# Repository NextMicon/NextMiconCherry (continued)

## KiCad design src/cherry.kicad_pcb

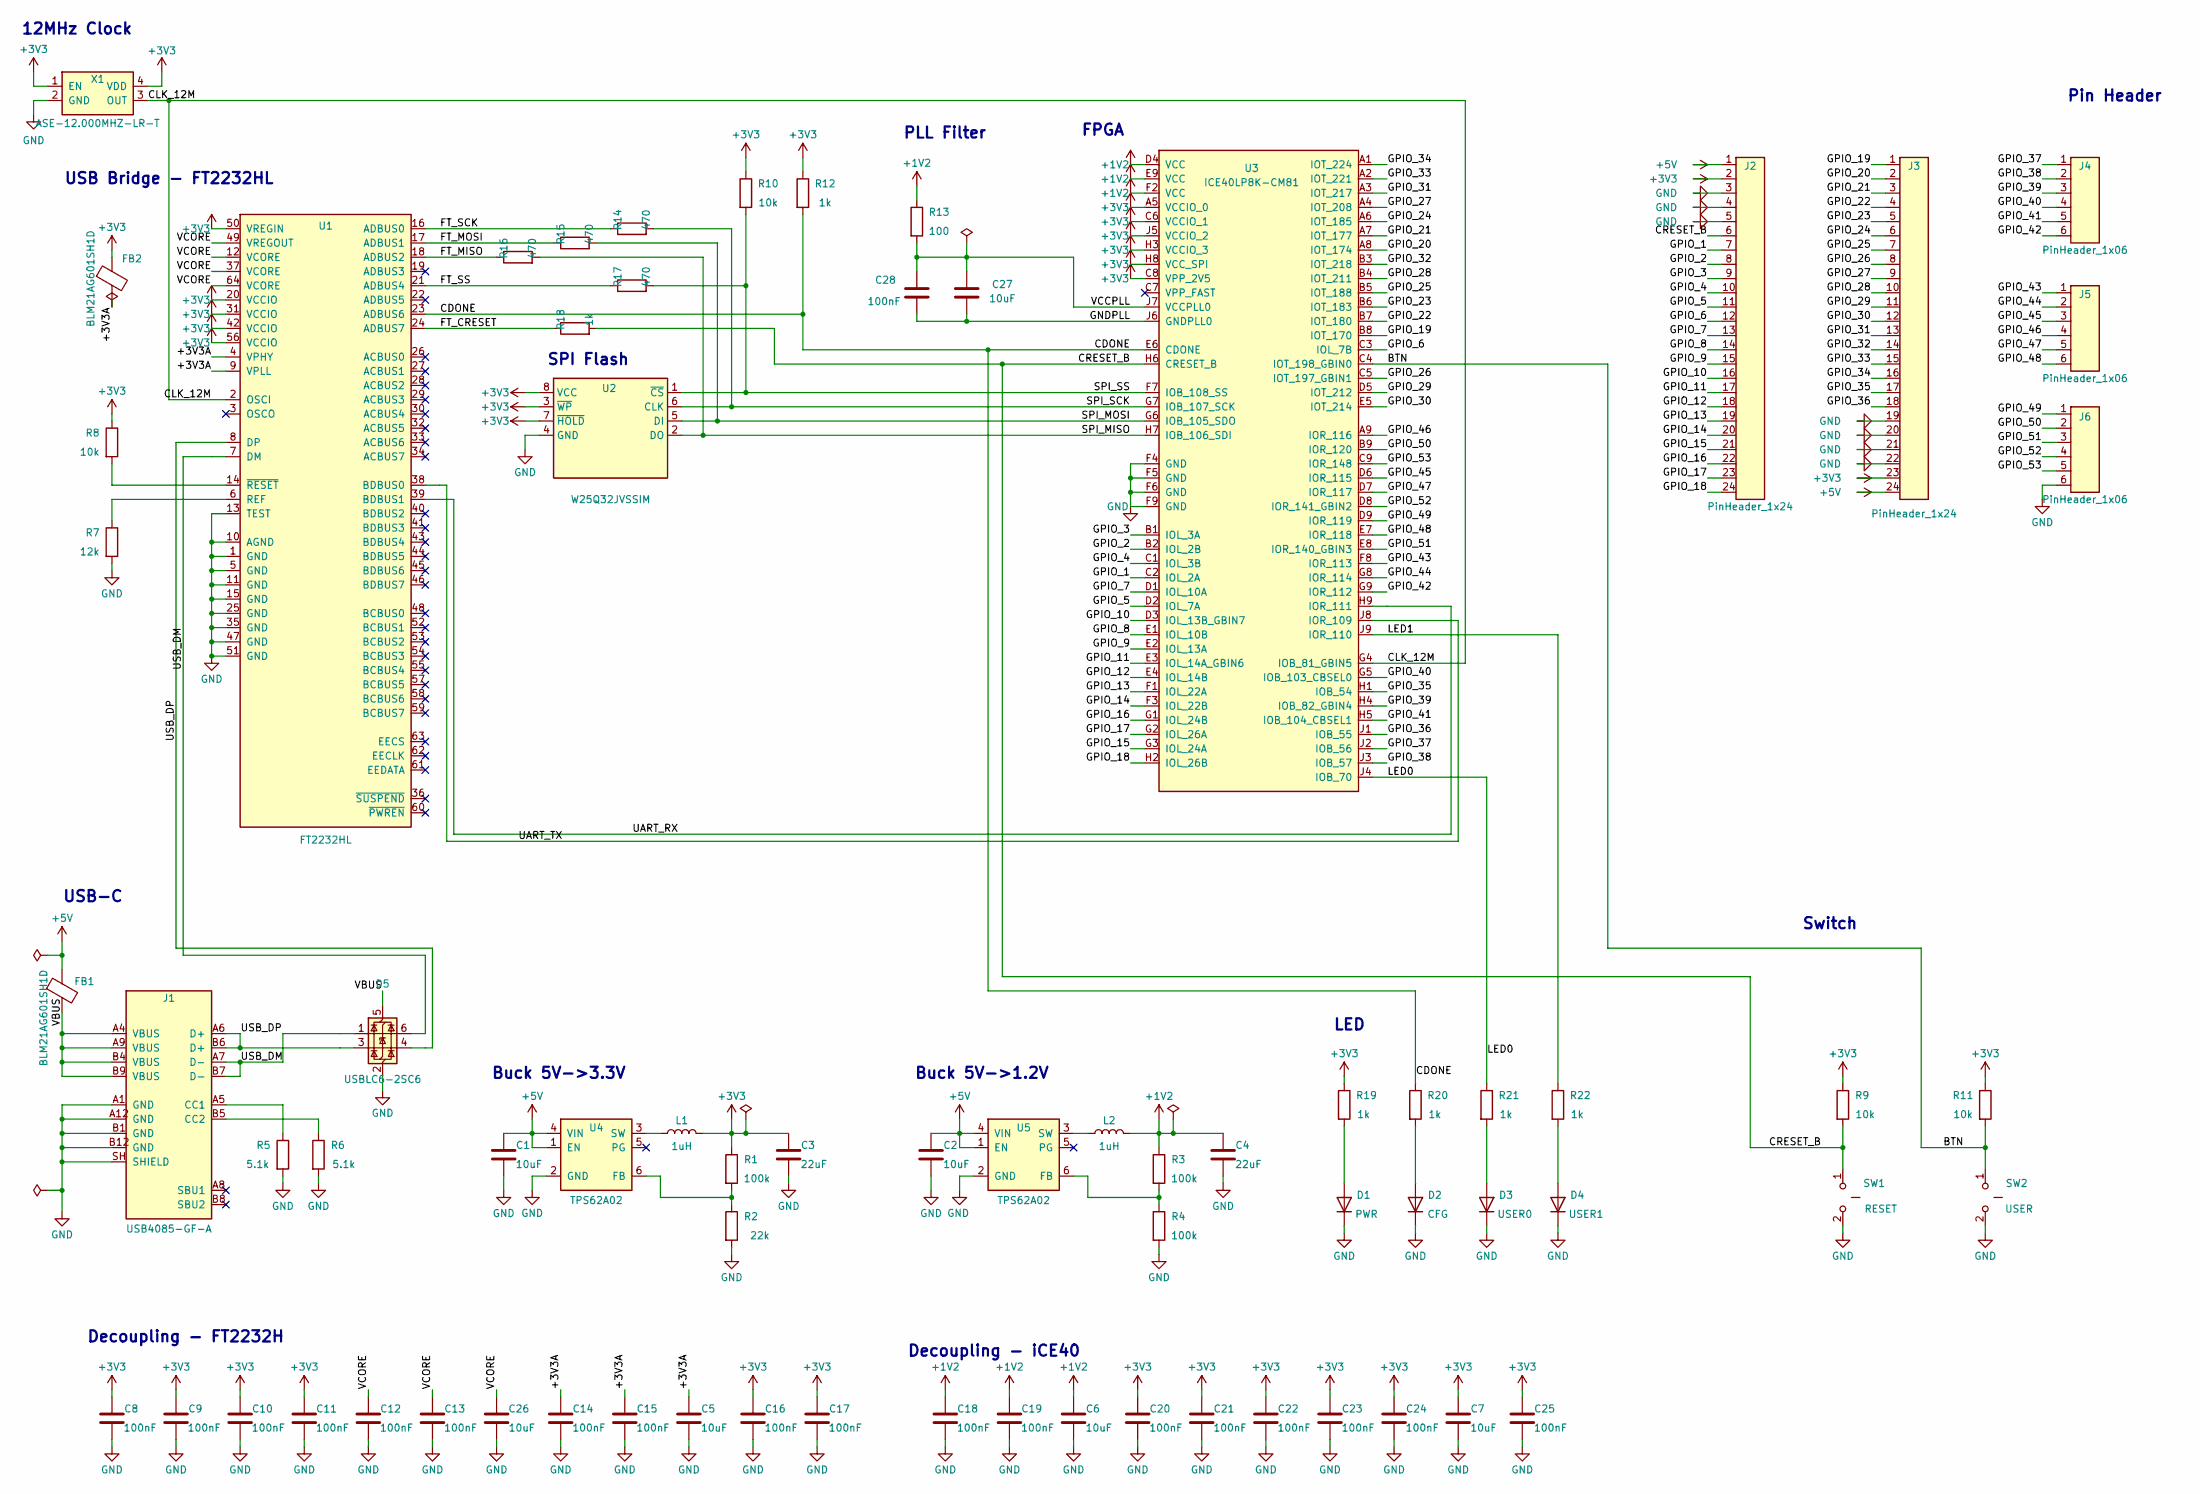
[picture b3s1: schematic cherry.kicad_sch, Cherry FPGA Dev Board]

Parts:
C1, C2, C5, C6, C7, C26, C27: 10uF; C_0805_2012Metric
C3, C4: 22uF; C_0805_2012Metric
C8, C9, C10, C11, C12, C13, C14, C15, C16, C17, C18, C19, C20, C21, C22, C23, C24, C25, C28: 100nF; C_0402_1005Metric
D1: PWR; LED_0603_1608Metric
D2: CFG; LED_0603_1608Metric
D3: USER0; LED_0603_1608Metric
D4: USER1; LED_0603_1608Metric
D5: USBLC6-2SC6; SOT-23-6
FB1, FB2: BLM21AG601SH1D; L_0805_2012Metric
J1: USB4085-GF-A; USB_C_Receptacle_GCT_USB4085
J2, J3: PinHeader_1x24; PinHeader_1x24_P2.54mm
J4, J5, J6: PinHeader_1x06; PinHeader_1x06_P2.54mm
L1, L2: 1uH; L_0805_2012Metric
R1, R3, R4: 100k; R_0402_1005Metric
R2: 22k; R_0402_1005Metric
R5, R6: 5.1k; R_0402_1005Metric
R7: 12k; R_0402_1005Metric
R8, R9, R10, R11: 10k; R_0402_1005Metric
R12, R18, R19, R20, R21, R22: 1k; R_0402_1005Metric
R13: 100; R_0402_1005Metric
R14, R15, R16, R17: 470; R_0402_1005Metric
SW1: RESET; SW_Push_1P1T_NO_CK_KMR2
SW2: USER; SW_Push_1P1T_NO_CK_KMR2
U1: FT2232HL; LQFP-64_10x10mm_P0.5mm
U2: W25Q32JVSSIM; SOIC-8_5.3x5.3mm_P1.27mm
U3: ICE40LP8K-CM81; BGA-81_9x9_8.0x8.0mm_P0.8mm
U4, U5: TPS62A02; SOT-23-6
X1: ASE-12.000MHZ-LR-T; Oscillator_SMD_Abracon_ASE-4Pin_3.2x2.5mm

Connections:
+1V2: C4.1, C6.1, C18.1, C19.1, L2.2, R3.1, R13.1, U3.D4 (VCC), U3.E9 (VCC), U3.F2 (VCC)
+3V3: C3.1, C7.1, C8.1, C9.1, C10.1, C11.1, C16.1, C17.1, C20.1, C21.1, C22.1, C23.1, C24.1, C25.1, FB2.1, J2.2, J3.23, L1.2, R1.1, R8.1, R9.1, R10.1, R11.1, R12.1, R19.1, U1.20 (VCCIO), U1.31 (VCCIO), U1.42 (VCCIO), U1.50 (VREGIN), U1.56 (VCCIO), U2.3 (~WP), U2.7 (~HOLD), U2.8 (VCC), U3.A5 (VCCIO_0), U3.C6 (VCCIO_1), U3.C8 (VPP_2V5), U3.H3 (VCCIO_3), U3.H8 (VCC_SPI), U3.J5 (VCCIO_2), X1.1 (EN), X1.4 (VDD)
+5V: C1.1, C2.1, FB1.1, J2.1, J3.24, U4.1 (EN), U4.4 (VIN), U5.1 (EN), U5.4 (VIN)
/+3V3A: C5.1, C14.1, C15.1, FB2.2, U1.4 (VPHY), U1.9 (VPLL)
/BTN: R11.2, SW2.1, U3.C4 (IOT_198_GBIN0)
/CDONE: R12.2, R20.1, U1.23 (ADBUS6), U3.E6 (CDONE)
/CLK_12M: U1.2 (OSCI), U3.G4 (IOB_81_GBIN5), X1.3 (OUT)
/CRESET_B: J2.6, R9.2, R18.2, SW1.1, U3.H6 (CRESET_B)
/FT_CRESET: R18.1, U1.24 (ADBUS7)
/FT_MISO: R16.1, U1.18 (ADBUS2)
/FT_MOSI: R15.1, U1.17 (ADBUS1)
/FT_SCK: R14.1, U1.16 (ADBUS0)
/FT_SS: R17.1, U1.21 (ADBUS4)
/GNDPLL: C27.2, C28.2, U3.J6 (GNDPLL0)
/GPIO_1: J2.7, U3.C2 (IOL_2A)
/GPIO_2: J2.8, U3.B2 (IOL_2B)
/GPIO_3: J2.9, U3.B1 (IOL_3A)
/GPIO_4: J2.10, U3.C1 (IOL_3B)
/GPIO_5: J2.11, U3.D2 (IOL_7A)
/GPIO_6: J2.12, U3.C3 (IOL_7B)
/GPIO_7: J2.13, U3.D1 (IOL_10A)
/GPIO_8: J2.14, U3.E1 (IOL_10B)
/GPIO_9: J2.15, U3.E2 (IOL_13A)
/GPIO_10: J2.16, U3.D3 (IOL_13B_GBIN7)
/GPIO_11: J2.17, U3.E3 (IOL_14A_GBIN6)
/GPIO_12: J2.18, U3.E4 (IOL_14B)
/GPIO_13: J2.19, U3.F1 (IOL_22A)
/GPIO_14: J2.20, U3.F3 (IOL_22B)
/GPIO_15: J2.21, U3.G3 (IOL_24A)
/GPIO_16: J2.22, U3.G1 (IOL_24B)
/GPIO_17: J2.23, U3.G2 (IOL_26A)
/GPIO_18: J2.24, U3.H2 (IOL_26B)
/GPIO_19: J3.1, U3.B8 (IOT_170)
/GPIO_20: J3.2, U3.A8 (IOT_174)
/GPIO_21: J3.3, U3.A7 (IOT_177)
/GPIO_22: J3.4, U3.B7 (IOT_180)
/GPIO_23: J3.5, U3.B6 (IOT_183)
/GPIO_24: J3.6, U3.A6 (IOT_185)
/GPIO_25: J3.7, U3.B5 (IOT_188)
/GPIO_26: J3.8, U3.C5 (IOT_197_GBIN1)
/GPIO_27: J3.9, U3.A4 (IOT_208)
/GPIO_28: J3.10, U3.B4 (IOT_211)
/GPIO_29: J3.11, U3.D5 (IOT_212)
/GPIO_30: J3.12, U3.E5 (IOT_214)
/GPIO_31: J3.13, U3.A3 (IOT_217)
/GPIO_32: J3.14, U3.B3 (IOT_218)
/GPIO_33: J3.15, U3.A2 (IOT_221)
/GPIO_34: J3.16, U3.A1 (IOT_224)
/GPIO_35: J3.17, U3.H1 (IOB_54)
/GPIO_36: J3.18, U3.J1 (IOB_55)
/GPIO_37: J4.1, U3.J2 (IOB_56)
/GPIO_38: J4.2, U3.J3 (IOB_57)
/GPIO_39: J4.3, U3.H4 (IOB_82_GBIN4)
/GPIO_40: J4.4, U3.G5 (IOB_103_CBSEL0)
/GPIO_41: J4.5, U3.H5 (IOB_104_CBSEL1)
/GPIO_42: J4.6, U3.G9 (IOR_112)
/GPIO_43: J5.1, U3.F8 (IOR_113)
/GPIO_44: J5.2, U3.G8 (IOR_114)
/GPIO_45: J5.3, U3.D6 (IOR_115)
/GPIO_46: J5.4, U3.A9 (IOR_116)
/GPIO_47: J5.5, U3.D7 (IOR_117)
/GPIO_48: J5.6, U3.E7 (IOR_118)
/GPIO_49: J6.1, U3.D9 (IOR_119)
/GPIO_50: J6.2, U3.B9 (IOR_120)
/GPIO_51: J6.3, U3.E8 (IOR_140_GBIN3)
/GPIO_52: J6.4, U3.D8 (IOR_141_GBIN2)
/GPIO_53: J6.5, U3.C9 (IOR_148)
/LED0: R21.1, U3.J4 (IOB_70)
/LED1: R22.1, U3.J9 (IOR_110)
/SPI_MISO: R16.2, U2.2 (DO), U3.H7 (IOB_106_SDI)
/SPI_MOSI: R15.2, U2.5 (DI), U3.G6 (IOB_105_SDO)
/SPI_SCK: R14.2, U2.6 (CLK), U3.G7 (IOB_107_SCK)
/SPI_SS: R10.2, R17.2, U2.1 (~CS), U3.F7 (IOB_108_SS)
/UART_RX: U1.39 (BDBUS1), U3.H9 (IOR_111)
/UART_TX: U1.38 (BDBUS0), U3.J8 (IOR_109)
/USB_DM: D5.1 (I/O1), D5.6 (I/O1), J1.A7 (D-), J1.B7 (D-), U1.7 (DM)
/USB_DP: D5.3 (I/O2), D5.4 (I/O2), J1.A6 (D+), J1.B6 (D+), U1.8 (DP)
/VBUS: D5.5 (VBUS), FB1.2, J1.A4 (VBUS), J1.A9 (VBUS), J1.B4 (VBUS), J1.B9 (VBUS)
/VCCPLL: C27.1, C28.1, R13.2, U3.J7 (VCCPLL0)
/VCORE: C12.1, C13.1, C26.1, U1.12 (VCORE), U1.37 (VCORE), U1.49 (VREGOUT), U1.64 (VCORE)
GND: C1.2, C2.2, C3.2, C4.2, C5.2, C6.2, C7.2, C8.2, C9.2, C10.2, C11.2, C12.2, C13.2, C14.2, C15.2, C16.2, C17.2, C18.2, C19.2, C20.2, C21.2, C22.2, C23.2, C24.2, C25.2, C26.2, D1.1 (K), D2.1 (K), D3.1 (K), D4.1 (K), D5.2 (GND), J1.A1 (GND), J1.A12 (GND), J1.B1 (GND), J1.B12 (GND), J1.SH (SHIELD), J2.3, J2.4, J2.5, J3.19, J3.20, J3.21, J3.22, J6.6, R2.2, R4.2, R5.2, R6.2, R7.2, SW1.2, SW2.2, U1.1 (GND), U1.5 (GND), U1.10 (AGND), U1.11 (GND), U1.13 (TEST), U1.15 (GND), U1.25 (GND), U1.35 (GND), U1.47 (GND), U1.51 (GND), U2.4 (GND), U3.F4 (GND), U3.F5 (GND), U3.F6 (GND), U3.F9 (GND), U4.2 (GND), U5.2 (GND), X1.2 (GND)
unnamed: D1.2 (A), R19.2
unnamed: D2.2 (A), R20.2
unnamed: D3.2 (A), R21.2
unnamed: D4.2 (A), R22.2
unnamed: J1.A5 (CC1), R5.1
unnamed: J1.B5 (CC2), R6.1
unnamed: R7.1, U1.6 (REF)
unnamed: R8.2, U1.14 (~RESET)
unnamed: R1.2, R2.1, U4.6 (FB)
unnamed: L1.1, U4.3 (SW)
unnamed: R3.2, R4.1, U5.6 (FB)
unnamed: L2.1, U5.3 (SW)

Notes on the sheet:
Switch
Buck 5V->3.3V
Decoupling - FT2232H
Pin Header
USB Bridge - FT2232HL
Buck 5V->1.2V
FPGA
PLL Filter
LED
USB-C
12MHz Clock
SPI Flash
Decoupling - iCE40

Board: 4 copper layers, 73 parts (5 on the bottom side), 93 nets, no tracks yet.

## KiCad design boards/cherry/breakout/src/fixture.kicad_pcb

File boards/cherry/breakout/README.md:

# Cherry Pmod breakout board

Cherryのピンヘッダ(J2/J3/J4)を上から**ピンソケット(S2/S3/S4)に挿し込み**、全64本のGPIOを8ポートのPmod(2×6、12ピン)として引き出すブレークアウト基板です。工場テスト(factory-test.sh)と、Pmodモジュールを挿しての動作確認の両方に使えます。

## ポート構成

| ポート | GPIO | 位置 |
| ------ | ---------- | -------- |
| PMOD1  | GPIO_1-8   | 下辺 左 |
| PMOD2  | GPIO_9-16  | 下辺 中左 |
| PMOD3  | GPIO_17-24 | 下辺 中右 |
| PMOD4  | GPIO_25-32 | 下辺 右 |
| PMOD5  | GPIO_33-40 | 上辺 右 |
| PMOD6  | GPIO_41-48 | 上辺 中右 |
| PMOD7  | GPIO_49-56 | 上辺 中左 |
| PMOD8  | GPIO_57-64 | 上辺 左 |

Cherry側のGPIOはブロック対配置(D0-D3が内側列、D4-D7がその対向の外側列)なので、各Pmodポートは Cherry の1つの2×4ブロックにそのまま対応します。各ポートのピン配置はPmod標準どおり: 1-4 = D0-D3、5 = GND、6 = 3V3、7-10 = D4-D7、11 = GND、12 = 3V3。D0が各ブロックの最小GPIO番号です(例: PMOD5のD0 = GPIO_33)。Pmodソケットは2×6のライトアングル・メスを基板端向きに実装します(実装前にピン1の向きをシルクの角パッドで確認してください)。

- S2/S3: 2×24ピンソケット。Cherry J2/J3が挿さります(ソケットのピン番号 = Cherryのパッド番号)。
- S4: 1×6ピンソケット。Cherry J4が挿さります。
- J5: Cherry J4のSPI/CRESET/GNDを引き出す1×6ピンヘッダ(右辺)。
- J6: +5V / +3V3 / GND / CRESET_B のユーティリティ、1×6ピンヘッダ(左辺)。
- USB-CはCherry本体へ直接接続します。基板にはUSB回路を載せません。
- F.Fabレイヤの破線はCherry外形、MH1--MH4はM3スタンドオフ用です。

電源はGND(裏面ベタ)と+3V3(表面ベタ)のゾーンで配電し、Cherryの全GND/3V3ピンとPmodの電源ピンを共通ネットに接続しています。GPIOと SPI/CRESET は1:1配線です。ソケットピンと引き出し先の対応は[`pinmap.csv`](pinmap.csv)を参照してください(`fixture_ref`はソケット:パッド番号、`dut_pin`はコネクタ位置1..24、`breakout_pin`は引き出し先)。

[`src/fixture.kicad_pcb`](src/fixture.kicad_pcb)は[`tools/gen_fixture.py`](tools/gen_fixture.py)で生成しています(配線・ゾーン込み。再生成後は pcbnew Python でゾーンを塗り直してください)。座標や割当を変えるときは手編集せずスクリプトを直して再生成してください。

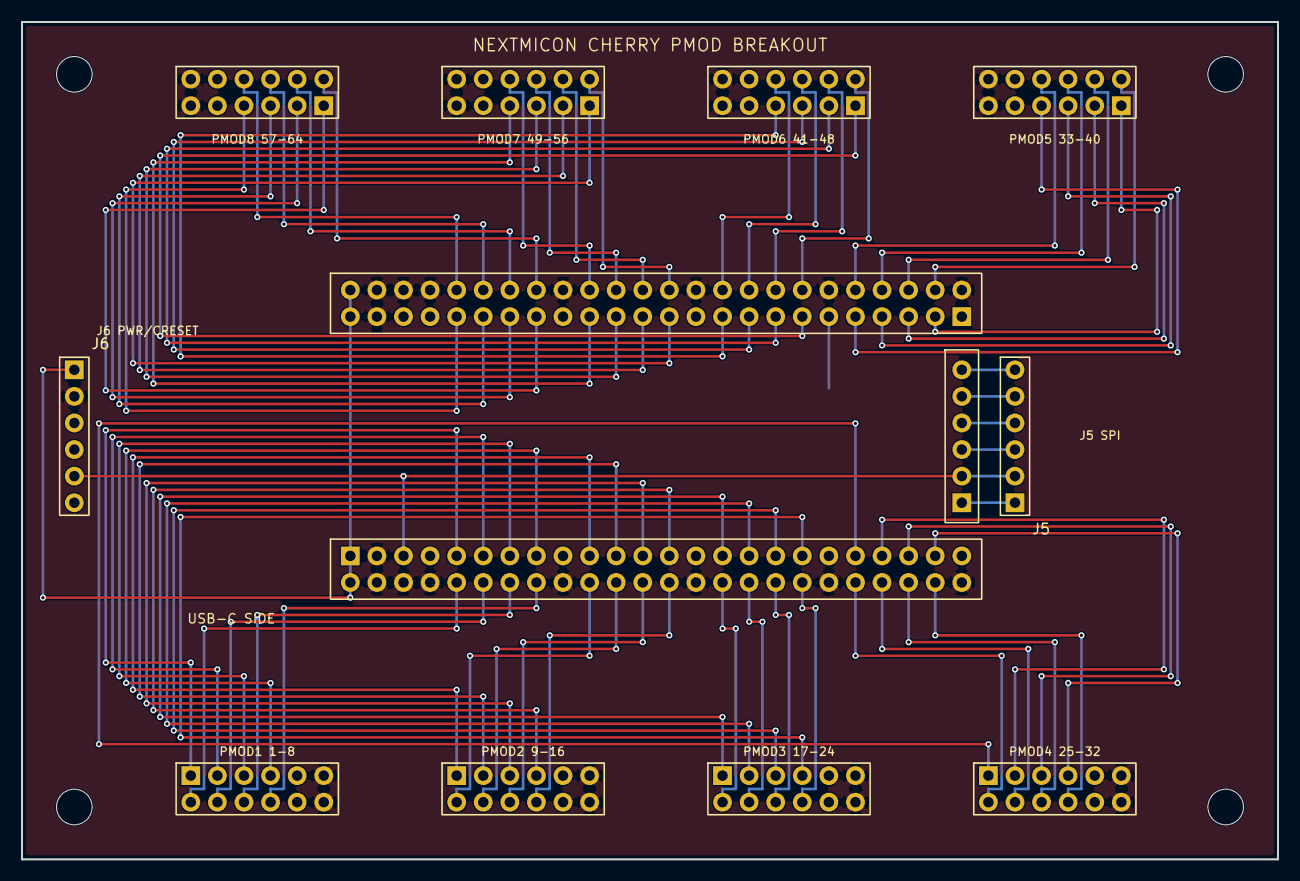
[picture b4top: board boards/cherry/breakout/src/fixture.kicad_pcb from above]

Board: 2 copper layers, 120.0 x 80.0 mm, 13 parts (0 on the bottom side), 72 nets.

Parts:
J5, J6: Header_1x6
PMOD1, PMOD2, PMOD3, PMOD4, PMOD5, PMOD6, PMOD7, PMOD8: Pmod_2x6
S2: Socket_S2
S3: Socket_S3
S4: Socket_S4

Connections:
+3V3: J6.2 (+3V3), PMOD1.6 (+3V3), PMOD1.12 (+3V3), PMOD2.6 (+3V3), PMOD2.12 (+3V3), PMOD3.6 (+3V3), PMOD3.12 (+3V3), PMOD4.6 (+3V3), PMOD4.12 (+3V3), PMOD5.6 (+3V3), PMOD5.12 (+3V3), PMOD6.6 (+3V3), PMOD6.12 (+3V3), PMOD7.6 (+3V3), PMOD7.12 (+3V3), PMOD8.6 (+3V3), PMOD8.12 (+3V3), S2.3 (+3V3), S2.4 (+3V3), S2.6 (+3V3), S2.8 (+3V3), S2.18 (+3V3), S2.28 (+3V3), S2.38 (+3V3), S2.48 (+3V3), S3.2 (+3V3), S3.12 (+3V3), S3.22 (+3V3), S3.32 (+3V3), S3.42 (+3V3), S3.44 (+3V3), S3.45 (+3V3), S3.46 (+3V3)
+5V: J6.1 (+5V), S2.1 (+5V), S2.2 (+5V), S3.47 (+5V), S3.48 (+5V)
CRESET_B: J5.2 (CRESET_B), J6.5 (CRESET_B), S2.5 (CRESET_B), S4.2 (CRESET_B)
GND: J5.1 (GND), J6.3 (GND), J6.4 (GND), J6.6 (GND), PMOD1.5 (GND), PMOD1.11 (GND), PMOD2.5 (GND), PMOD2.11 (GND), PMOD3.5 (GND), PMOD3.11 (GND), PMOD4.5 (GND), PMOD4.11 (GND), PMOD5.5 (GND), PMOD5.11 (GND), PMOD6.5 (GND), PMOD6.11 (GND), PMOD7.5 (GND), PMOD7.11 (GND), PMOD8.5 (GND), PMOD8.11 (GND), S2.7 (GND), S2.17 (GND), S2.27 (GND), S2.37 (GND), S2.47 (GND), S3.1 (GND), S3.11 (GND), S3.21 (GND), S3.31 (GND), S3.41 (GND), S3.43 (GND), S4.1 (GND)
GPIO1: PMOD1.1 (GPIO1), S2.9 (GPIO1)
GPIO2: PMOD1.2 (GPIO2), S2.11 (GPIO2)
GPIO3: PMOD1.3 (GPIO3), S2.13 (GPIO3)
GPIO4: PMOD1.4 (GPIO4), S2.15 (GPIO4)
GPIO5: PMOD1.7 (GPIO5), S2.10 (GPIO5)
GPIO6: PMOD1.8 (GPIO6), S2.12 (GPIO6)
GPIO7: PMOD1.9 (GPIO7), S2.14 (GPIO7)
GPIO8: PMOD1.10 (GPIO8), S2.16 (GPIO8)
GPIO9: PMOD2.1 (GPIO9), S2.19 (GPIO9)
GPIO10: PMOD2.2 (GPIO10), S2.21 (GPIO10)
GPIO11: PMOD2.3 (GPIO11), S2.23 (GPIO11)
GPIO12: PMOD2.4 (GPIO12), S2.25 (GPIO12)
GPIO13: PMOD2.7 (GPIO13), S2.20 (GPIO13)
GPIO14: PMOD2.8 (GPIO14), S2.22 (GPIO14)
GPIO15: PMOD2.9 (GPIO15), S2.24 (GPIO15)
GPIO16: PMOD2.10 (GPIO16), S2.26 (GPIO16)
GPIO17: PMOD3.1 (GPIO17), S2.29 (GPIO17)
GPIO18: PMOD3.2 (GPIO18), S2.31 (GPIO18)
GPIO19: PMOD3.3 (GPIO19), S2.33 (GPIO19)
GPIO20: PMOD3.4 (GPIO20), S2.35 (GPIO20)
GPIO21: PMOD3.7 (GPIO21), S2.30 (GPIO21)
GPIO22: PMOD3.8 (GPIO22), S2.32 (GPIO22)
GPIO23: PMOD3.9 (GPIO23), S2.34 (GPIO23)
GPIO24: PMOD3.10 (GPIO24), S2.36 (GPIO24)
GPIO25: PMOD4.1 (GPIO25), S2.39 (GPIO25)
GPIO26: PMOD4.2 (GPIO26), S2.41 (GPIO26)
GPIO27: PMOD4.3 (GPIO27), S2.43 (GPIO27)
GPIO28: PMOD4.4 (GPIO28), S2.45 (GPIO28)
GPIO29: PMOD4.7 (GPIO29), S2.40 (GPIO29)
GPIO30: PMOD4.8 (GPIO30), S2.42 (GPIO30)
GPIO31: PMOD4.9 (GPIO31), S2.44 (GPIO31)
GPIO32: PMOD4.10 (GPIO32), S2.46 (GPIO32)
GPIO33: PMOD5.1 (GPIO33), S3.3 (GPIO33)
GPIO34: PMOD5.2 (GPIO34), S3.5 (GPIO34)
GPIO35: PMOD5.3 (GPIO35), S3.7 (GPIO35)
GPIO36: PMOD5.4 (GPIO36), S3.9 (GPIO36)
GPIO37: PMOD5.7 (GPIO37), S3.4 (GPIO37)
GPIO38: PMOD5.8 (GPIO38), S3.6 (GPIO38)
GPIO39: PMOD5.9 (GPIO39), S3.8 (GPIO39)
GPIO40: PMOD5.10 (GPIO40), S3.10 (GPIO40)
GPIO41: PMOD6.1 (GPIO41), S3.13 (GPIO41)
GPIO42: PMOD6.2 (GPIO42), S3.15 (GPIO42)
GPIO43: PMOD6.3 (GPIO43), S3.17 (GPIO43)
GPIO44: PMOD6.4 (GPIO44), S3.19 (GPIO44)
GPIO45: PMOD6.7 (GPIO45), S3.14 (GPIO45)
GPIO46: PMOD6.8 (GPIO46), S3.16 (GPIO46)
GPIO47: PMOD6.9 (GPIO47), S3.18 (GPIO47)
GPIO48: PMOD6.10 (GPIO48), S3.20 (GPIO48)
GPIO49: PMOD7.1 (GPIO49), S3.23 (GPIO49)
GPIO50: PMOD7.2 (GPIO50), S3.25 (GPIO50)
GPIO51: PMOD7.3 (GPIO51), S3.27 (GPIO51)
GPIO52: PMOD7.4 (GPIO52), S3.29 (GPIO52)
GPIO53: PMOD7.7 (GPIO53), S3.24 (GPIO53)
GPIO54: PMOD7.8 (GPIO54), S3.26 (GPIO54)
GPIO55: PMOD7.9 (GPIO55), S3.28 (GPIO55)
GPIO56: PMOD7.10 (GPIO56), S3.30 (GPIO56)
GPIO57: PMOD8.1 (GPIO57), S3.33 (GPIO57)
GPIO58: PMOD8.2 (GPIO58), S3.35 (GPIO58)
GPIO59: PMOD8.3 (GPIO59), S3.37 (GPIO59)
GPIO60: PMOD8.4 (GPIO60), S3.39 (GPIO60)
GPIO61: PMOD8.7 (GPIO61), S3.34 (GPIO61)
GPIO62: PMOD8.8 (GPIO62), S3.36 (GPIO62)
GPIO63: PMOD8.9 (GPIO63), S3.38 (GPIO63)
GPIO64: PMOD8.10 (GPIO64), S3.40 (GPIO64)
QSPI_CS_B: J5.3 (QSPI_CS_B), S4.3 (QSPI_CS_B)
QSPI_MISO: J5.6 (QSPI_MISO), S4.6 (QSPI_MISO)
QSPI_MOSI: J5.5 (QSPI_MOSI), S4.5 (QSPI_MOSI)
QSPI_SCK: J5.4 (QSPI_SCK), S4.4 (QSPI_SCK)

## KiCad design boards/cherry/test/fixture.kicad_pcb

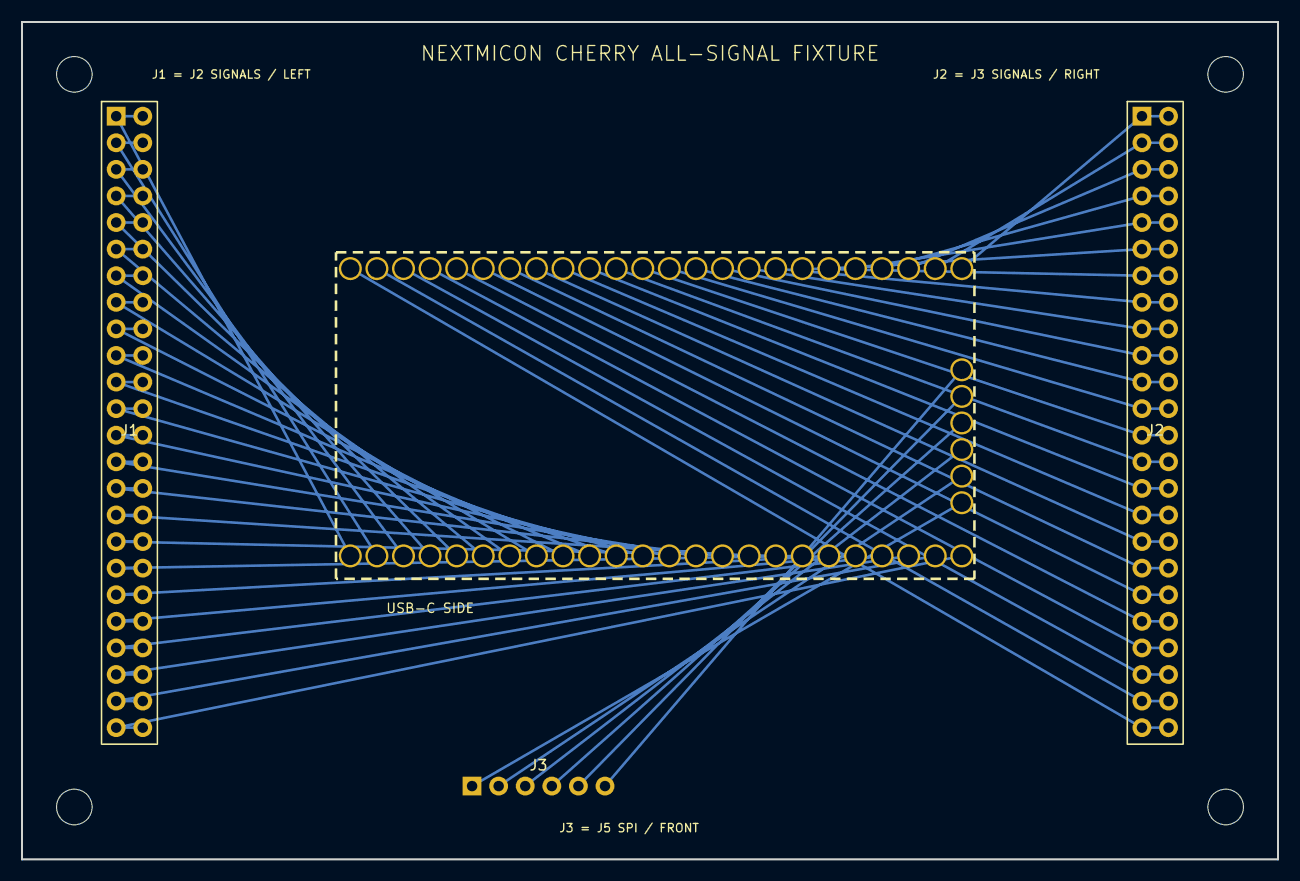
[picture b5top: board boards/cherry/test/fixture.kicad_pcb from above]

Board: 2 copper layers, 120.0 x 80.0 mm, 57 parts (0 on the bottom side), 44 nets.

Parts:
J1, J2: Header_2x24
J3: Header_1x06
P_J2_1, P_J2_2, P_J2_3, P_J2_4, P_J2_5, P_J2_6, P_J2_7, P_J2_8, P_J2_9, P_J2_10, P_J2_11, P_J2_12, P_J2_13, P_J2_14, P_J2_15, P_J2_16, P_J2_17, P_J2_18, P_J2_19, P_J2_20, P_J2_21, P_J2_22, P_J2_23, P_J2_24, P_J3_1, P_J3_2, P_J3_3, P_J3_4, P_J3_5, P_J3_6, P_J3_7, P_J3_8, P_J3_9, P_J3_10, P_J3_11, P_J3_12, P_J3_13, P_J3_14, P_J3_15, P_J3_16, P_J3_17, P_J3_18, P_J3_19, P_J3_20, P_J3_21, P_J3_22, P_J3_23, P_J3_24, P_J5_1, P_J5_2, P_J5_3, P_J5_4, P_J5_5, P_J5_6: pogo

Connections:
+3V3: J1.2 (+3V3), J2.23 (+3V3), P_J2_2.1 (P_J2_2), P_J3_23.1 (P_J3_23)
+5V: J1.1 (+5V), J2.24 (+5V), P_J2_1.1 (P_J2_1), P_J3_24.1 (P_J3_24)
CRESET_B: J1.6 (CRESET_B), J3.2 (CRESET_B), P_J2_6.1 (P_J2_6), P_J5_2.1 (P_J5_2)
GND: J1.3 (GND), J1.4 (GND), J1.5 (GND), J2.19 (GND), J2.20 (GND), J2.21 (GND), J2.22 (GND), J3.1 (GND), P_J2_3.1 (P_J2_3), P_J2_4.1 (P_J2_4), P_J2_5.1 (P_J2_5), P_J3_19.1 (P_J3_19), P_J3_20.1 (P_J3_20), P_J3_21.1 (P_J3_21), P_J3_22.1 (P_J3_22), P_J5_1.1 (P_J5_1)
GPIO1: J1.7 (GPIO1), P_J2_7.1 (P_J2_7)
GPIO2: J1.8 (GPIO2), P_J2_8.1 (P_J2_8)
GPIO3: J1.9 (GPIO3), P_J2_9.1 (P_J2_9)
GPIO4: J1.10 (GPIO4), P_J2_10.1 (P_J2_10)
GPIO5: J1.11 (GPIO5), P_J2_11.1 (P_J2_11)
GPIO6: J1.12 (GPIO6), P_J2_12.1 (P_J2_12)
GPIO7: J1.13 (GPIO7), P_J2_13.1 (P_J2_13)
GPIO8: J1.14 (GPIO8), P_J2_14.1 (P_J2_14)
GPIO9: J1.15 (GPIO9), P_J2_15.1 (P_J2_15)
GPIO10: J1.16 (GPIO10), P_J2_16.1 (P_J2_16)
GPIO11: J1.17 (GPIO11), P_J2_17.1 (P_J2_17)
GPIO12: J1.18 (GPIO12), P_J2_18.1 (P_J2_18)
GPIO13: J1.19 (GPIO13), P_J2_19.1 (P_J2_19)
GPIO14: J1.20 (GPIO14), P_J2_20.1 (P_J2_20)
GPIO15: J1.21 (GPIO15), P_J2_21.1 (P_J2_21)
GPIO16: J1.22 (GPIO16), P_J2_22.1 (P_J2_22)
GPIO17: J1.23 (GPIO17), P_J2_23.1 (P_J2_23)
GPIO18: J1.24 (GPIO18), P_J2_24.1 (P_J2_24)
GPIO19: J2.1 (GPIO19), P_J3_1.1 (P_J3_1)
GPIO20: J2.2 (GPIO20), P_J3_2.1 (P_J3_2)
GPIO21: J2.3 (GPIO21), P_J3_3.1 (P_J3_3)
GPIO22: J2.4 (GPIO22), P_J3_4.1 (P_J3_4)
GPIO23: J2.5 (GPIO23), P_J3_5.1 (P_J3_5)
GPIO24: J2.6 (GPIO24), P_J3_6.1 (P_J3_6)
GPIO25: J2.7 (GPIO25), P_J3_7.1 (P_J3_7)
GPIO26: J2.8 (GPIO26), P_J3_8.1 (P_J3_8)
GPIO27: J2.9 (GPIO27), P_J3_9.1 (P_J3_9)
GPIO28: J2.10 (GPIO28), P_J3_10.1 (P_J3_10)
GPIO29: J2.11 (GPIO29), P_J3_11.1 (P_J3_11)
GPIO30: J2.12 (GPIO30), P_J3_12.1 (P_J3_12)
GPIO31: J2.13 (GPIO31), P_J3_13.1 (P_J3_13)
GPIO32: J2.14 (GPIO32), P_J3_14.1 (P_J3_14)
GPIO33: J2.15 (GPIO33), P_J3_15.1 (P_J3_15)
GPIO34: J2.16 (GPIO34), P_J3_16.1 (P_J3_16)
GPIO35: J2.17 (GPIO35), P_J3_17.1 (P_J3_17)
GPIO36: J2.18 (GPIO36), P_J3_18.1 (P_J3_18)
QSPI_CS_B: J3.3 (QSPI_CS_B), P_J5_3.1 (P_J5_3)
QSPI_MISO: J3.6 (QSPI_MISO), P_J5_6.1 (P_J5_6)
QSPI_MOSI: J3.5 (QSPI_MOSI), P_J5_5.1 (P_J5_5)
QSPI_SCK: J3.4 (QSPI_SCK), P_J5_4.1 (P_J5_4)

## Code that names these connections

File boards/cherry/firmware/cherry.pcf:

# NextMicon Cherry / iCE40HX8K-BG121 pin constraints
#
# Yosys generates the JSON netlist; nextpnr-ice40 consumes this PCF.
# Port names are from the FPGA point of view.  GPIO names match the
# one-based labels printed on the board schematic.

# Fixed board resources
set_io clk_48m E10
set_io btn      C4
set_io led0     J4
set_io led1     J3
set_io led2     J5
set_io led3     K5

# Optional runtime aliases.  These pins are shared with QSPI_IO3 and PROG_LED.
set_io uart_rx  J8
set_io uart_tx  J10

# Logical GPIO numbering. All 64 header GPIOs have independent HX8K balls;
# the native USB D-, D+ and pull-up-control nets remain dedicated.
# GPIO_1..32 are on J2 and GPIO_33..64 on J3. Each block of eight occupies
# one 2x4 window: D0-D3 on the inner (odd) row and D4-D7 directly opposite
# on the outer (even) row of the same connector positions.
set_io gpio_1  C2
set_io gpio_2  B2
set_io gpio_3  B1
set_io gpio_4  C1
set_io gpio_5  A2
set_io gpio_6  A1
set_io gpio_7  H1
set_io gpio_8  J1

set_io gpio_9  D2
set_io gpio_10 C3
set_io gpio_11 D1
set_io gpio_12 E1
set_io gpio_13 F2
set_io gpio_14 F4
set_io gpio_15 H3
set_io gpio_16 J2

set_io gpio_17 E2
set_io gpio_18 D3
set_io gpio_19 E3
set_io gpio_20 A5
set_io gpio_21 K1
set_io gpio_22 K2
set_io gpio_23 L1
set_io gpio_24 L2

set_io gpio_25 F1
set_io gpio_26 F3
set_io gpio_27 G3
set_io gpio_28 G1
set_io gpio_29 K3
set_io gpio_30 L3
set_io gpio_31 L4
set_io gpio_32 K4

set_io gpio_33 G2
set_io gpio_34 H2
set_io gpio_35 B8
set_io gpio_36 A8
set_io gpio_37 D7
set_io gpio_38 A10
set_io gpio_39 A11
set_io gpio_40 B11

set_io gpio_41 A7
set_io gpio_42 B7
set_io gpio_43 B6
set_io gpio_44 A6
set_io gpio_45 C11
set_io gpio_46 D9
set_io gpio_47 D10
set_io gpio_48 D11

set_io gpio_49 B5
set_io gpio_50 C7
set_io gpio_51 A9
set_io gpio_52 B9
set_io gpio_53 E8
set_io gpio_54 E9
set_io gpio_55 E11
set_io gpio_56 F9

set_io gpio_57 D5
set_io gpio_58 C8
set_io gpio_59 C9
set_io gpio_60 B3
set_io gpio_61 F10
set_io gpio_62 G8
set_io gpio_63 G10
set_io gpio_64 G11

# J4 is the six-pin header reserved for external SPI flash programming.

# Reserved configuration bus.  These balls are shared by the W25Q32 and FPGA.
# Do not expose them as ordinary user outputs.
# set_io flash_cs_n K10
# set_io flash_mosi K9
# set_io flash_sck  L10
# set_io flash_miso J9
# QSPI_IO2 uses K6 and QSPI_IO3 uses J8 in user mode.
# CBSEL0 uses L8 for the boot/user selector. CBSEL1 uses H9 and is held low.

# Dedicated configuration pins (CRESET_B L9 and CDONE K8) are not user I/O.
# clk_48m/E10 is driven by X1 and must only be declared as an FPGA input.

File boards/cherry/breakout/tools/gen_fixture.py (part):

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    return cols

# signal tables
J2_IN  = ['+5V','+3V3','CRESET_B','GND','GPIO1','GPIO2','GPIO3','GPIO4','GND','GPIO9','GPIO10','GPIO11','GPIO12','GND','GPIO17','GPIO18','GPIO19','GPIO20','GND','GPIO25','GPIO26','GPIO27','GPIO28','GND']
J2_OUT = ['+5V','+3V3','+3V3','+3V3','GPIO5','GPIO6','GPIO7','GPIO8','+3V3','GPIO13','GPIO14','GPIO15','GPIO16','+3V3','GPIO21','GPIO22','GPIO23','GPIO24','+3V3','GPIO29','GPIO30','GPIO31','GPIO32','+3V3']
J3_IN  = ['GND','GPIO33','GPIO34','GPIO35','GPIO36','GND','GPIO41','GPIO42','GPIO43','GPIO44','GND','GPIO49','GPIO50','GPIO51','GPIO52','GND','GPIO57','GPIO58','GPIO59','GPIO60','GND','GND','+3V3','+5V']
J3_OUT = ['+3V3','GPIO37','GPIO38','GPIO39','GPIO40','+3V3','GPIO45','GPIO46','GPIO47','GPIO48','+3V3','GPIO53','GPIO54','GPIO55','GPIO56','+3V3','GPIO61','GPIO62','GPIO63','GPIO64','+3V3','+3V3','+3V3','+5V']
J4SIG  = ['GND','CRESET_B','QSPI_CS_B','QSPI_SCK','QSPI_MOSI','QSPI_MISO']
J6SIG  = ['+5V','+3V3','GND','GND','CRESET_B','GND']   # J6 pin1..6 top->bottom

def gsrc(n):
    """source pogo (x, y) for GPIO n (opposed-block layout)"""
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             'PMOD5': list(range(33,41)),'PMOD6': list(range(41,49)),
             'PMOD7': list(range(49,57)),'PMOD8': list(range(57,65))}

netnames = ['GND','+5V','+3V3','CRESET_B','QSPI_CS_B','QSPI_SCK','QSPI_MOSI','QSPI_MISO'] + [f'GPIO{i}' for i in range(1,65)]
netno = {n:i+1 for i,n in enumerate(netnames)}

_uid = [0]
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via(7.0, YJ6(1), '+5V')
hseg(YJ6(1), 7.0, X_J6, '+5V')

# CRESET_B: one straight F.Cu lane at y=48.39 from J6.5 to P_J4_2 pad, tapping P_J2_3
hseg(48.39, X_J6, X_PJ4, 'CRESET_B')
via(41.45, 48.39, 'CRESET_B')
vseg(41.45, 48.39, Y_J2_IN, 'CRESET_B')
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
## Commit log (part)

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2026-05-31 chore
